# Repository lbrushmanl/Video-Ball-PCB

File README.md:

# Video-Ball-PCB

http://www.pong-story.com/eaus0576.htm This is where I got the information about building this.

All I have done is take the PCB layout from the magazine and import it into Kicad (It took a long time as all the holes had to be added manually).
I have also made the silk screen for the PCB as the original one from the magazine could not be converted very well to black and white.
Some of the schematics has also been recreated.

No jumpers are required, but they are still on the silk screen.

Image of PCB

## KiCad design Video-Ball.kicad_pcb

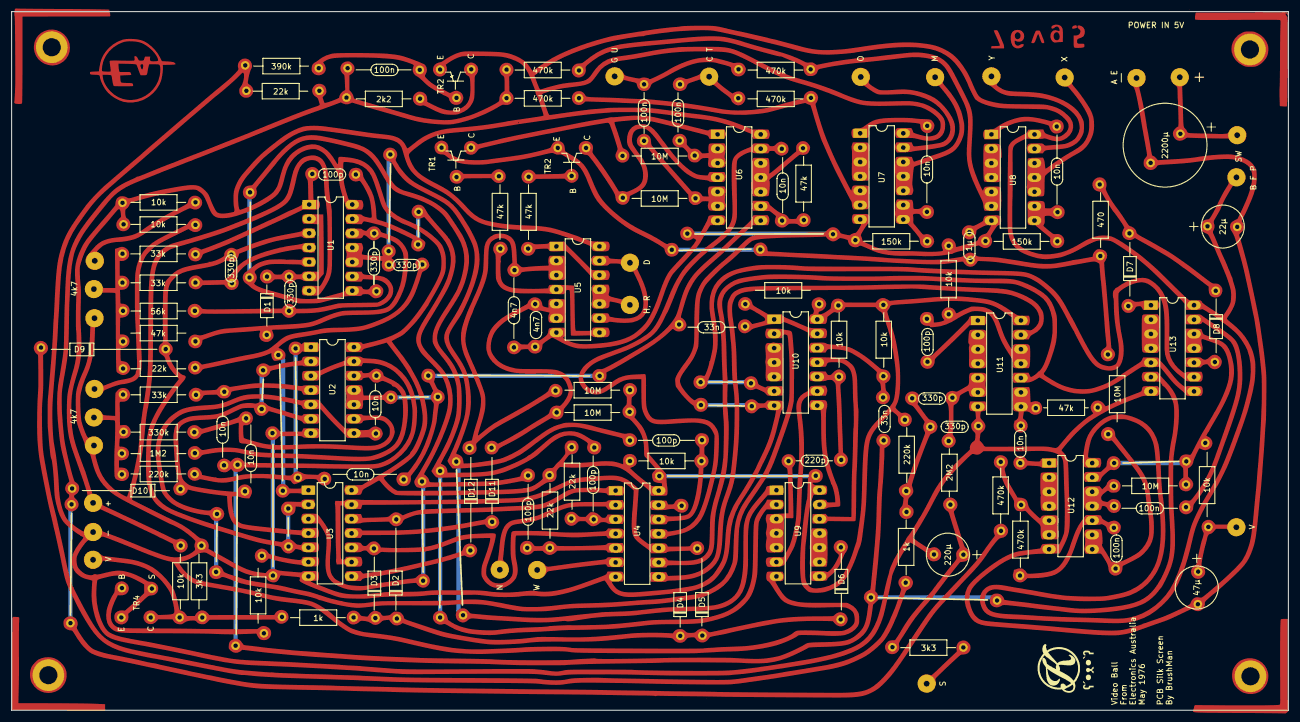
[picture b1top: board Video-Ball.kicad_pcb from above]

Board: 2 copper layers, 225.7 x 123.5 mm, 13 parts (0 on the bottom side), 4 nets.

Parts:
U1, U2, U3, U5, U6, U7, U8, U9, U10, U11, U12, U13: 74HC00; DIP-14_W7.62mm_LongPads
U4: 74HC02; DIP-14_W7.62mm_LongPads

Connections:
/BL: U1.4, U1.8
/CL: U1.9, U1.11
GND: U1.7 (GND), U3.7 (GND)
unnamed: U1.1, U1.6

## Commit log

2023-01-13 PCB Files Added
2023-02-18 Fixed incorrect silk screen said HR and D under IC U1 should be a 330pF cap
